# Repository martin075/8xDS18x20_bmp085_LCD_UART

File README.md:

# 8xDS18x20_bmp085_LCD_UART
it is continue of Tom Blough's termometer. contain Davide Gironi libs BMP085.calculation of pressure must be checked.
project in Atmel Studio 4.18, atmel tool chain 3.4.4, avr-gcc 4.8.1, Fleury's libs uart, twi, i2c updated, Atmega168 8 MHz internal
DS18b20, DS18s20, LCD lib

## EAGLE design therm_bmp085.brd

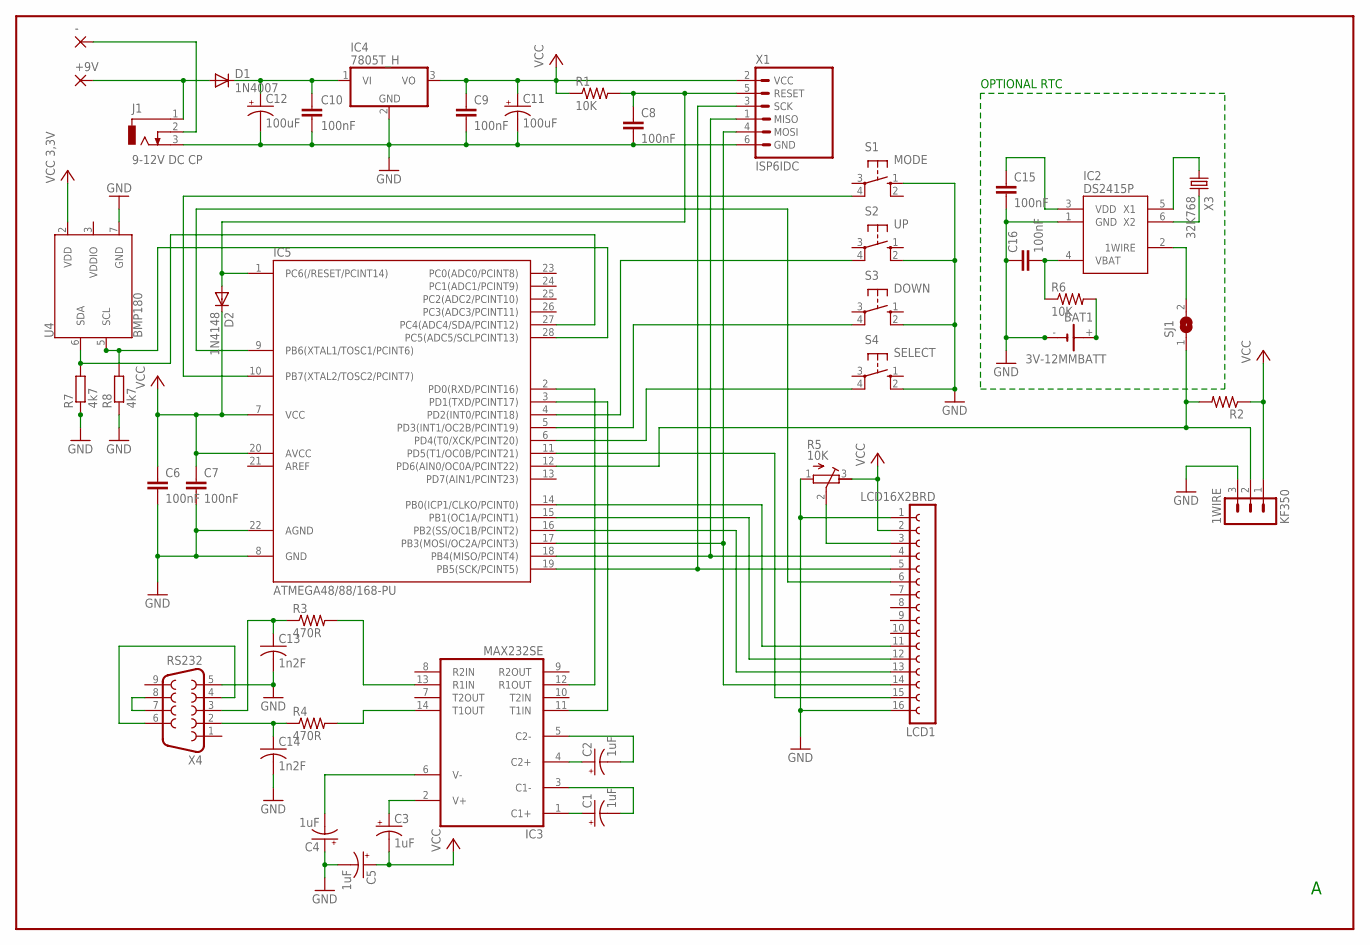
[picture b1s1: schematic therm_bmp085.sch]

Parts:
1WIRE: KF350
+9V: WIREPAD3,17/1,1; 3,17/1,1
-: WIREPAD3,17/1,1; 3,17/1,1
BAT1: 3V-12MMBATT; KEYELCO3001
C1, C2, C3, C4, C5: 1uF; CT3528
C6, C7, C8, C15, C16: 100nF; C0805
C9, C10: 100nF; C025_050-024X070
C11, C12: 100uF; E2,5-7
C13, C14: 1n2F; C0805
D1: 1N4007; D-10
D2: 1N4148; DO34-7
IC2: DS2415P; TSOC6
IC3: MAX232SE; SO16
IC4: 7805T_H; TO220H
IC5: ATMEGA48/88/168-PU; DIL28-3
J1: 9-12V DC CP; DCJ0202
LCD1: LCD16X2BRD; LCD16X2
R1, R6: 10K; R0805
R2: R-US_0207/10; 0207/10
R3, R4: 470R; R0805
R5: 10K; RTRIM5X
R7, R8: 4k7; 0204V
S1: MODE; B3F-10XX
S2: UP; B3F-10XX
S3: DOWN; B3F-10XX
S4: SELECT; B3F-10XX
SJ1: SJ
U4: BMP180
X1: ISP6IDC; IDC-6
X3: 32K768; TC38H_SMD
X4: RS232; F09D

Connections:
+9V: +9V.1, D1.A, J1.1
GND: 1WIRE.3, BAT1.-, BAT1.-1, BAT1.-2, BAT1.-3, C4.+, C5.-, C6.2, C7.2, C8.2, C9.2, C10.3 (1), C11.-, C12.-, C13.2, C14.2, C15.2, C16.1, IC2.1 (GND), IC3.15 (GND), IC4.2 (GND), IC5.8 (GND), IC5.22 (AGND), J1.3, LCD1.1, LCD1.16, R5.1 (E), R7.1, R8.1, S1.1 (S), S2.2 (S1), S3.2 (S1), S4.2 (S1), U4.7 (GND), X1.6 (GND), X4.5
unnamed: C10.2, C12.+, D1.C, IC4.1 (VI)
unnamed: C3.+, IC3.2 (V+)
unnamed: C4.-, IC3.6 (V-)
unnamed: IC3.12 (R1OUT), IC5.2 (PD0(RXD/PCINT16))
unnamed: IC3.11 (T1IN), IC5.3 (PD1(TXD/PCINT17))
unnamed: C14.1, R4.1, X4.2
unnamed: IC3.14 (T1OUT), R4.2
unnamed: C13.1, R3.1, X4.3
unnamed: IC3.13 (R1IN), R3.2
unnamed: X4.7, X4.8
unnamed: X4.4, X4.6
unnamed: C1.+, IC3.1 (C1+)
unnamed: C1.-, IC3.3 (C1-)
unnamed: C2.-, IC3.5 (C2-)
unnamed: C2.+, IC3.4 (C2+)
unnamed: LCD1.3, R5.2 (S)
unnamed: IC5.10 (PB7(XTAL2/TOSC2/PCINT7)), S1.4 (P1)
unnamed: IC5.9 (PB6(XTAL1/TOSC1/PCINT6)), LCD1.6
unnamed: IC5.19 (PB5(SCK/PCINT5)), LCD1.5, X1.3 (SCK)
unnamed: IC5.18 (PB4(MISO/PCINT4)), LCD1.4, X1.1 (MISO)
unnamed: IC5.17 (PB3(MOSI/OC2A/PCINT3)), LCD1.14, X1.4 (MOSI)
unnamed: IC5.16 (PB2(SS/OC1B/PCINT2)), LCD1.13
unnamed: IC5.15 (PB1(OC1A/PCINT1)), LCD1.12
unnamed: IC5.14 (PB0(ICP1/CLKO/PCINT0)), LCD1.11
unnamed: IC5.11 (PD5(T1/OC0B/PCINT21)), LCD1.15
unnamed: IC5.4 (PD2(INT0/PCINT18)), S2.4 (P1)
unnamed: IC5.5 (PD3(INT1/OC2B/PCINT19)), S3.4 (P1)
unnamed: IC5.6 (PD4(T0/XCK/PCINT20)), S4.4 (P1)
unnamed: 1WIRE.2, IC5.12 (PD6(AIN0/OC0A/PCINT22)), R2.2, SJ1.1
unnamed: IC2.6 (X2), X3.P$2 (2)
unnamed: IC2.5 (X1), X3.P$1 (1)
unnamed: C8.1, D2.A, IC5.1 (PC6(/RESET/PCINT14)), R1.2, X1.5 (RESET)
unnamed: -.1, J1.2
unnamed: IC2.2 (1WIRE), SJ1.2
unnamed: C15.1, IC2.3 (VDD)
unnamed: BAT1.+, BAT1.+1, R6.2
unnamed: IC5.27 (PC4(ADC4/SDA/PCINT12)), IC5.28 (PC5(ADC5/SCLPCINT13)), R7.2, R8.2, U4.5 (SCL), U4.6 (SDA)
VBAT: C16.2, IC2.4 (VBAT), R6.1
VCC: 1WIRE.1, C3.-, C5.+, C6.1, C7.1, C9.3 (1), C11.+, D2.C, IC3.16 (VCC), IC4.3 (VO), IC5.7 (VCC), IC5.20 (AVCC), LCD1.2, R1.1, R2.1, R5.3 (A), U4.2 (VDD), X1.2 (VCC)

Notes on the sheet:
OPTIONAL RTC

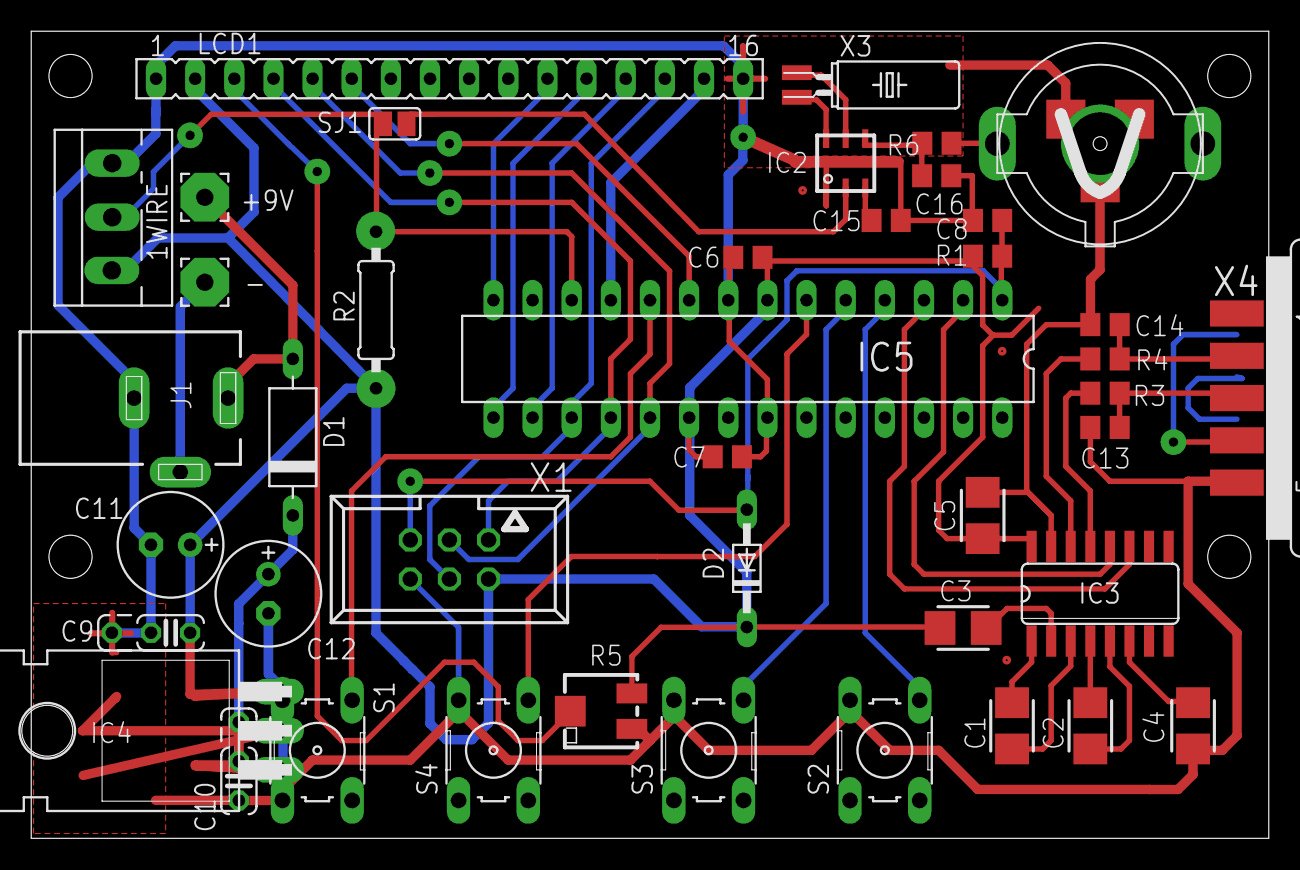
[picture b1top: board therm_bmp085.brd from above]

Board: 2 copper layers, 80.3 x 52.4 mm, 42 parts (0 on the bottom side), 40 nets.

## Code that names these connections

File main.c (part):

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*                do not mix 18b20 family and 1820/18s20
*
* Host Configuration ATMega16:
*	PB0  LCD_DATA_4
*	PB1  LCD_DATA_5
*	PB2  LCD_DATA_6
*	PB3  LCD_DATA_7
*	PB4  LCD_DATA_RS
*	PB5  LCD_DATA_R/W
*	PB6  LCD_DATA_E
*
*	PD0  RxD, 19200,8,n,1
*	PD1  TxD
*	PD6  1-Wire Data, external 15K pullup
*	PD7  PWM LCD Backlight (OC2)
*
*	PB7  momentary MODE button
*	PD2  momentary UP/LEFT/FORWARD button
*	PD3  momentary DOWN/RIGHT/BACK button
*	PD4  momentary SELECTION button
*
* Host Configuration ATMega168, 8MHz:
*  note- on STK500, PB6 and PB7 are not routed to PortB header
*  instead they are routed to PortE XT1/XT2
*	PB0  LCD_DATA_4
*	PB1  LCD_DATA_5
*	PB2  LCD_DATA_6
*	PB3  LCD_DATA_7
*	PB4  LCD_DATA_RS
*	PB5  LCD_DATA_R/W
*	PB6  LCD_DATA_E
*
*	PD0  RxD, 19200,8,n,1
*	PD1  TxD
*	PD6  1-Wire Data, external 15K pullup
*	PD5  PWM LCD Backlight (OC2)
*
*	PB7  momentary MODE button
*	PD2  momentary UP/LEFT/FORWARD button
*	PD3  momentary DOWN/RIGHT/BACK button
*	PD4  momentary SELECTION button
*/

#include <stdio.h>
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uint8_t EEMEM nvgSensorIDs8[OWI_ROMCODE_SIZE];

// buttons - checks if pressed and returns 0x01 or 0 if not pressed
#define BTN_MODE ((~PINB & (1 << PB7)) >> PB7)
#define BTN_UP ((~PIND & (1 << PD2)) >> PD2)
#define BTN_DOWN ((~PIND & (1 << PD3)) >> PD3)	
#define BTN_SEL ((~PIND & (1 << PD4)) >> PD4)	

// custom characters for LCD display
static const PROGMEM unsigned char lcdChars[] =
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	DDRD &= ~(1 << PD7);
	PORTD |= (1 << PD7);
#elif defined(__AVR_ATmega16__)
	DDRD &= ~(1 << PD5);
	PORTD |= (1 << PD5);
#else
#error "Unknown target device"
#endif
	
	// enable our push buttons
	DDRB &= ~(1 << PB7);	// set for input - button 1
	PORTB |= (1 << PB7);	// enable pull-up
	DDRD &= ~((1 << PD2) | (1 << PD3) | (1 << PD4));	// buttons 2,3,4
	PORTD |= (1 << PD2) | (1 << PD3) | (1 << PD4);

	// set up PWM for LCD backlight control
#if defined(__AVR_ATmega168__)
#define PWM_OUT OCR0B
	DDRD |= _BV( PD5);	// OC0B pin as output
	TCCR0A = _BV( WGM00) | _BV( WGM01) | _BV( COM0B1);	// Fast PWM, CTC+TOP
	TCCR0B = _BV( CS01);	// 1/8 prescale
#elif defined(__AVR_ATmega16__)
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
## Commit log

2017-03-21 :tada: Added .gitattributes & .gitignore files
2017-03-23 barometric presure to sea level - formula
2017-03-24 ch
    offset to sea level
2017-04-03 board scheme in eagle
2017-04-03 add
    description

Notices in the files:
parts and their libraries:
SparkFun-Sensors: Licensing: Creative Commons ShareAlike 4.0 International - https://creativecommons.org/licenses/by-sa/4.0
